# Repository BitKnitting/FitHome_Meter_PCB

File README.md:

Kicad is used to create the schematic and layout.
# Meter PCB
The meter PCB takes in the voltage and current readings from the Power PCB and uses two atm90e26 energy monitor ICs to convert the readings to DC readings.  The DC readings are sent to the microcontroller over SPI. The Meter PCB is one of the three PCBs that make up the FitHome hardware.  The other two are the:  
* [The Power PCB](https://github.com/BitKnitting/FitHome_Power_PCB)  monitors the incoming voltage and current of a (North American's) home energy lines.  
* [The microcontroller PCB](https://github.com/BitKnitting/Tisham_PCB_Feather).  The microcontroller PCB mounts a microcontroller with wifi - like a Feather RFM95 or a wemos D1 (a bit up in the air as of this date - 4/5/2019).  The microcontroller gets the voltage and current readings from the atm90e26's over SPI and then sends them via mqtt.
# Thanks to Those That Went Before
This project extends [Tisham Dhar's work on building energy monitors using an atm90e26](https://github.com/whatnick/DIN_Rail_EnergyMonitor).  In particular, [the DIN Rail energy monitor](https://www.crowdsupply.com/whatnick/atm90e26-energy-monitor-kits).  Besides his open source projects, Tisham has been exceptionally helpful and supportive.  Tisham continues to inspire me.  THANK YOU.

Before I took [Chris Gammell's Contextual Electronics course](https://contextualelectronics.com/), I had absolutely no experience with electronics or building PCBs.  Chris is exceptional in so many ways.  THANK YOU.

There is an exceptional community behind [the OpenEnergyMonitor project](https://learn.openenergymonitor.org/).  They not only provide energy monitoring solutions, but are a wealth of knowledge.  THANK YOU.
# The Schematic
## atm90e26
The two atm90e26's are the protagonists of the schematic.  

The voltage readings (VP_0 and VP_1) read by [the Power PCB](https://github.com/BitKnitting/FitHome_Power_PCB) are inputs to pins 16 and 15.  Similarly, the current readings (I1P_0 and I1P_1) are inputs to pins 10 and 11.  Recall that power comes into a house in North America through [two power lines](https://en.wikipedia.org/wiki/Split-phase_electric_power).  This is why there are two atm90e26's.

The atm90e26 is flexible in its Metering Mode configuration. The datasheet notes:

```
MMD1/0: Metering Mode Configuration
00: anti-tampering mode (larger power);
01: L line mode (fixed L line);
10: L+N mode (applicable for single-phase three-wire system);
11: flexible mode (line specified by the LNSel bit (MMode, 2BH))
```
We're only intested in L line mode (01). This is why pin 20 (MMD0) is set to GND and pin 1 (MMD1) is set to 3.3V.
## The Oscillator
As you probably know better than me, an oscillator is needed to generate clock signals to control the speed of the atm90e26's processor.  The datasheet notes using a crystal oscillator with a frequency of 8.192 MHz.  

### Why 20pF Caps
The datasheet states: _An 8.192 MHz crystal is connected between OSCI and OSCO. In application,
this pin should be connected to ground through a 12pF capacitor._  So why a 20pF cap if the datasheet states a 12p cap should be used.

I am following the advice of Tisham: _The BOM for the DIN rail uses a different crystal and hence different load capacitance (20pF)...Crystals are affected by board parasitics as well. Please see [the Adafruit article](https://blog.adafruit.com/2012/01/24/choosing-the-right-crystal-and-caps-for-your-design/) about this. The values I picked are only via rule of thumb. Try and see._  

The crystal being used is [PN AA-8.192MAGE-T](http://www.txccrystal.com/images/pdf/aa-automotive.pdf).  The datasheet states the Load Capacitance (CL) to be 8pF.  

Going on the advice in the Adafruit article, a "best estimate" for the capacitors (C1 and C2) is C1, C2 = 2*CL – 2*Cstray  where Cstray is described as: _Unfortunately, every trace, every lead on your component, just about everything on your PCB has some stray capacitance.  The total of these values is represented by Cstray.  You can usually guestimate this in the neighbourhood of 2-5pF as long as you follow good layout practice and keep the trace from the crystal to the pins on the MCU as short as possible with no vias, etc._

If we use Cstray = 3pF, 2*8 - 2*3 = 12pF - which is what is recommended in the datasheet. As of 4/10/2019 I am using 20pF based on Tisham's testing/recommendation.  If 20 doesn't work, I'll try 12pF and move up from there.  Challenges bring opportunities.

### My Frankenstein Test
I soldered an atm90e26 and the corresponding caps and resistors to get SPI working from the first meter PCB to an itsy bitsy.  I used Circuit Python and my Happyday_M90E26_SPI.py library to send SPI commands to the meter within the Mu editor.

#### Results
Sending request to read the System Status:
```
MOSI: 0x81;  MISO: 0xFF	
```
Value returned my atm90e26:  
```
MOSI: 0x00;  MISO: 0x00	
MOSI: 0x00;  MISO: 0x02	
```
OOH!  Isn't that GREAT?  System status = 2.  It is what I expected based on results I have gotten in the past.

Sending request to read the meter status:  
```
MOSI: 0xC6;  MISO: 0xFF	
```
Value returned: 
```
MOSI: 0x00;  MISO: 0xC8	
MOSI: 0x00;  MISO: 0x02	
```
Meter status = 0xC802.  I expected 0xC801.  

__TODO:__  
The Meter Status (46H) register notes that bits 1 - 0 when fixed L line (which I thought I had  i.e.: MMD1 = 0, MMD0 = 1) should be 01.  But the reading of 2 indicates MMD1 = 1 and MMD0 = 0.  Which is L+N mode.  __AHA!  I have this backword on the schematic.  So the meter status reading is correct given the current meter setting.  Currently, MMD1 is connected to +3.3V and MMD0 is connected to GND.__  
  
_ARGH.  The datasheet in the pin description led me to believe the MMD0 and 1 settings were reverse.  Then the description of the 46H register has it the reverse!  Well isn't that special!_
# Connectors
There are two connectors:  
* The male end of the PCI-E.  This is just a footprint on the PCB.  
* The PCB - PCB right angle 10 pin connector that connects the meter PCB to the uPCB.
## PCB - PCB connector
The one used is: 
* [52418-1010](https://www.mouser.com/datasheet/2/276/0524181010_PCB_RECEPTACLES-170490.pdf) molex Female side of connector.  These are around $1.22 each at [Digikey](https://www.digikey.com/product-detail/en/molex/52418-1010/WM6478-ND/481106) and $1.04 each at [Mouser](https://www.mouser.com/ProductDetail/538-52418-1010).  The Female is soldered onto the meter PCB.
* [53290-1080](https://www.molex.com/pdm_docs/sd/532901080_sd.pdf) male is $.82/each at [Digikey](https://www.digikey.com/product-detail/en/molex/53290-1080/WM24313-ND/917592) and $.90 each at[Mouser](https://www.mouser.com/ProductDetail/Molex/53290-1080?qs=%2Fha2pyFaduiHJk6fZnMcvUZuJ6ieM0yPA3e7l1ZVdEg%3D). The Male is soldered onto the uPCB.

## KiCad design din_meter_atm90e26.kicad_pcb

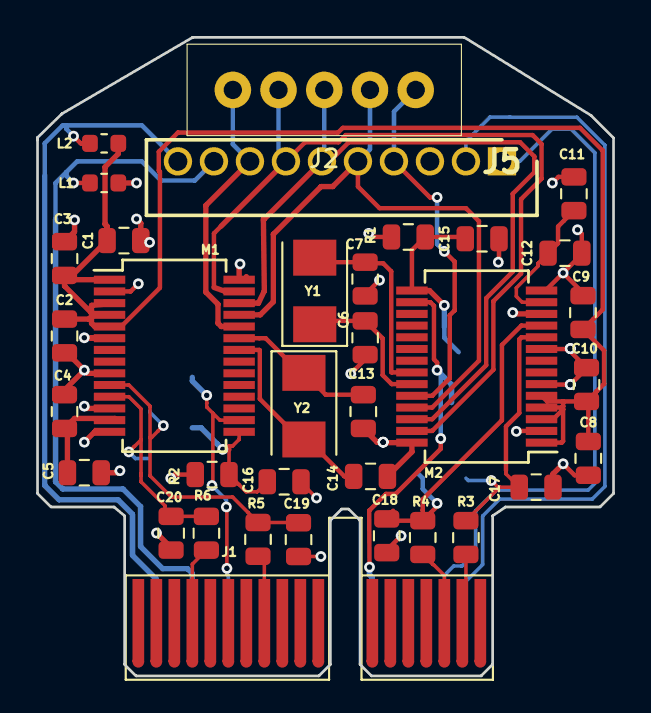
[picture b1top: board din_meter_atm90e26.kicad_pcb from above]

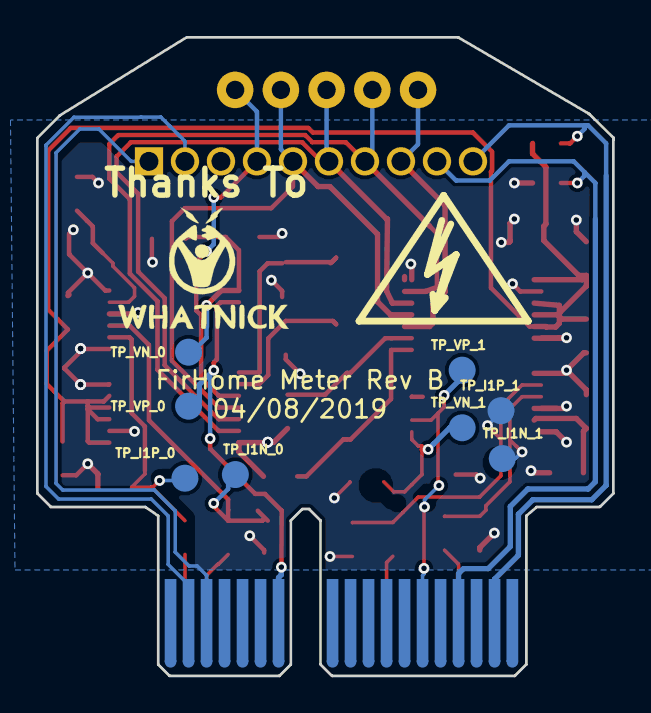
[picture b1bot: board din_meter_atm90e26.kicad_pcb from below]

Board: 2 copper layers, 32.0 x 35.5 mm, 45 parts (10 on the bottom side), 29 nets.

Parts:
C1, C4, C8, C11: 10u; C_0805_2012Metric
C2, C3, C5, C9, C10, C12: .1u; C_0805_2012Metric
C6, C7, C13, C14: 20p; C_0805_2012Metric
C15, C16, C17, C18, C19, C20: .033u; C_0805_2012Metric
G1: LOGO; Whatnick_logo
J1: PCI_Express; PCI-EXPRESS
J2: Conn_01x05; conn_5_2.54mm
J5: CONN_01X10; SHDR10W60P200_1X10_2150X400X335P
L1: GND_SUP; L_0603_1608Metric
L2: 3V3_SUP; L_0603_1608Metric
M1, M2: ATM90E26_ATM90E26; SSOP-28_5.3x10.2mm_Pitch0.65mm
R1, R2, R3, R4, R5, R6: 1K; R_0805_2012Metric
SYM1: SYM_Flash_Small; Fsilk_HV
TP_I1N_0: I1N_0; Measurement_Point_Round-SMD-Pad_Small
TP_I1N_1: I1N_1; Measurement_Point_Round-SMD-Pad_Small
TP_I1P_0: I1P_0; Measurement_Point_Round-SMD-Pad_Small
TP_I1P_1: I1P_1; Measurement_Point_Round-SMD-Pad_Small
TP_VN_0: VN_0; Measurement_Point_Round-SMD-Pad_Small
TP_VN_1: VN_1; Measurement_Point_Round-SMD-Pad_Small
TP_VP_0: VP_0; Measurement_Point_Round-SMD-Pad_Small
TP_VP_1: VP_1; Measurement_Point_Round-SMD-Pad_Small
Y1, Y2: Crystal_Small; Crystal_SMD_5032-2Pin_5.0x3.2mm

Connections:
3V3_CPU: J1.B17, J5.2
3V3_M: J1.B2, J5.10, L2.1
+3V3: C1.1, C2.2, C3.1, C8.1, C9.2, C10.1, L2.2, M1.1, M1.3, M1.4, M1.5, M2.1, M2.3, M2.4, M2.5
CLKIN_0: C7.2, M2.22, Y1.2
CLKIN_1: C14.2, M1.22, Y2.2
CLKOUT_0: C6.2, M2.23, Y1.1
CLKOUT_1: C13.2, M1.23, Y2.1
CS_0: J2.5, J5.4, M2.24
CS_1: J2.1, J5.8, M1.24
GNDD: C1.2, C2.1, C3.2, C4.2, C5.2, C6.1, C7.1, C8.2, C9.1, C10.2, C11.2, C12.2, C13.1, C14.1, C15.1, C16.1, C17.1, C18.1, C19.1, C20.1, L1.2, M1.2, M1.6, M1.9, M1.12, M1.14, M1.28, M2.2, M2.6, M2.9, M2.12, M2.14, M2.28, R1.2, R2.2
GND_CPU: J1.B16, J5.1
GND_M: J1.B4, J5.9, L1.1
I1N_0: C18.2, M2.11, R4.1, TP_I1N_0.1
I1N_0_IN: J1.A16, R4.2
I1N_1: C20.2, M1.11, R6.1, TP_I1N_1.1
I1N_1_IN: J1.A4, R6.2
I1P_0: C17.2, M2.10, R3.1, TP_I1P_0.1
I1P_0_IN: J1.A17, R3.2
I1P_1: C19.2, M1.10, R5.1, TP_I1P_1.1
I1P_1_IN: J1.A8, R5.2
MISO_M: J2.3, J5.6, M1.26, M2.26
MOSI_M: J2.2, J5.7, M1.27, M2.27
unnamed: C4.1, C5.1, M1.13
unnamed: C11.1, C12.1, M2.13
SCLK_M: J2.4, J5.5, M1.25, M2.25
VN_0: C15.2, M2.15, R1.1, TP_VN_0.1
VN_1: C16.2, M1.15, R2.1, TP_VN_1.1
VP_0: J1.B12, M2.16, TP_VP_0.1
VP_1: J1.B6, M1.16, TP_VP_1.1

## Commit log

2019-03-18 First commit.
2019-03-23 First pass at layout.
2019-03-25 Submitted to OSH Park & made Octopart BoM for v. A
2019-04-08 updated readme.
2019-04-08 OSH Park Rev B
